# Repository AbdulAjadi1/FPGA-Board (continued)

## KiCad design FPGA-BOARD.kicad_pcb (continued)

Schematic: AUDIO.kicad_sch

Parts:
C1, C2, C187, C189, C190, C191: 100nF; C_0201_0603Metric; LCSC PN c307380
C3: 820pF 5%; C_0402; LCSC PN c307452
C52: GA342DR7GF102KW02L; CAPC4520X220N; LCSC PN C237595
C175, C178: 1nF 5%; C_0402; LCSC PN c76947
C177: 150pF 5%; C_0402; LCSC PN c76951
C179: 100uF; C_0805; LCSC PN c141660
C180: T491B157M006AT; CAPMP3.7X2.8_2.1N_KEM
C182: 1uF 10V; C_0402; LCSC PN C52923
C183, C186: 100nF 10V; C_0402; LCSC PN C77020
C184: 10nF; C_0201_0603Metric; LCSC PN c85930
C185: 4.7uF; C_0402; LCSC PN C2858031
C188: 2.2uF; C_0402; LCSC PN c170151
CR3: BZT52C12-7-F; SOD123_DIO; LCSC PN C19077410
F2: PRG18BB330MB1RB; FUSE_PRG-18_MUR; LCSC PN C133974
J9: SJ1-3525NG; CUI_SJ1-3525NG
J15: USB-A-S-X-X-SM2; SAMTEC_USB-A-S-X-X-SM2; PARTREV T; LCSC PN C6906824
Q10: DMG2305UX-13; DMG2305UX_13; PARTREV 09/2018; LCSC PN C144153
R3, R16, R200, R201: 0; R_0402; LCSC PN C106231
R9: 1.3K 1%; R_0402; LCSC PN C185455
R10, R196: 2K 1%; R_0402; LCSC PN C60488
R11, R193: 10K 1%; R_0402; LCSC PN C60490
R12: 10.7K 1%; R_0402; LCSC PN C270654
R194, R195: 26.1K 1%; R_0402; LCSC PN C155697
R197: 100K; R_0402; LCSC PN C60491
R198: 1MEG; R_0402; LCSC PN C138033
R199: 330K; R_0402; LCSC PN c138006
R202: 4.7K; R_0201_0603Metric; LCSC PN C138135
R203: 1K; R_0402; LCSC PN C106235
U21: NC7WZ07P6X; MPN NC7WZ07P6X; LCSC PN C95342
U25: TPS2051BDBVR; DBV0005A_L; LCSC PN C24593
U26: TUSB1210BRHBT; RHB32_3P45X3P45; LCSC PN C2671015
U30: TPD4E05U06DQAR; IC_TPD4E05U06DQAR; PARTREV N; LCSC PN C138714
U36: AD8592ARM; RM_10_ADI
Y4: ABM8G-26.000MHZ-18-D2Y-T; CRYSTAL_ABM8G_ABR; LCSC PN C1985426

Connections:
+3V3: C184.2, C187.2, U26.20 (VDD33), U26.21 (VBAT), Y4.1, Y4.4 (VDD); also elsewhere on the board
+5V: C186.2, U25.5 (IN); also elsewhere on the board
AUD_PWM: U21.1 (A1); also elsewhere on the board
AUD_SD: U36.5, U36.6; also elsewhere on the board
AVCC3V3: C1.1, C2.1, R9.2, U21.5 (VCC), U36.10 (V+); also elsewhere on the board
GNDREF: C1.2, C2.2, C3.2, C52.1, C177.2, C180.2, C184.1, C185.1, C186.1, C187.1, C188.1, C189.1, C190.1, C191.1, J9.1, J15.04 (GND), R10.2, R193.1, R196.1, R197.2, R198.2, R199.2, R202.1, U21.2 (GND), U25.2 (GND), U26.23 (ID), U26.33 (EPAD), U26.V, U30.3 (GND), U30.8 (GND), U30.10 (NC_10), U36.4 (V-), Y4.2 (GND); also elsewhere on the board
unnamed: C175.1, R11.2, R12.1
unnamed: C175.2, R16.2, R194.2, U36.1
unnamed: C178.1, R194.1, R195.2
unnamed: C179.2, F2.1, R196.2
unnamed: C182.1, C183.1, CR3.2, Q10.1, R199.1, R200.2
unnamed: F2.2, J9.2
unnamed: J9.3, R197.1
unnamed: R3.2, R9.1, R10.1, R11.1
unnamed: R201.1, Y4.3
unnamed: R3.1, U21.6 (Y1)
unnamed: R202.2, U25.4 (EN), U26.17 (CPEN)
unnamed: C188.2, U26.12 (VDD15)
unnamed: C3.1, R12.2, U36.3 (+)
unnamed: R16.1, R193.2, U36.2 (-)
unnamed: C177.1, R195.1, U36.7 (+)
unnamed: C178.2, C179.1, U36.8 (-), U36.9
USBHOST_CLK: U26.26 (CLOCK); also elsewhere on the board
USBHOST_DATA0: U26.3 (DATA0); also elsewhere on the board
USBHOST_DATA1: U26.4 (DATA1); also elsewhere on the board
USBHOST_DATA2: U26.5 (DATA2); also elsewhere on the board
USBHOST_DATA3: U26.6 (DATA3); also elsewhere on the board
USBHOST_DATA4: U26.7 (DATA4); also elsewhere on the board
USBHOST_DATA5: U26.9 (DATA5); also elsewhere on the board
USBHOST_DATA6: U26.10 (DATA6); also elsewhere on the board
USBHOST_DATA7: U26.13 (DATA7); also elsewhere on the board
USBHOST_DIR: U26.31 (DIR); also elsewhere on the board
USBHOST_N: J15.02 (D-), U26.19 (DM), U30.2 (D1-)
USBHOST_NXT: U26.2 (NXT); also elsewhere on the board
USBHOST_OC: U25.3 (OC_N); also elsewhere on the board
USBHOST_P: J15.03 (D+), U26.18 (DP), U30.1 (D1+)
USBHOST_RCLK: R201.2, U26.1 (REFCLK)
USBHOST_RESETN: R203.1, U26.27 (RESETB); also elsewhere on the board
USBHOST_STP: U26.29 (STP); also elsewhere on the board
USBHOST_VBUS: C180.1, C183.2, C185.2, J15.01 (VCC), Q10.3, U26.22 (VBUS), U30.4 (D2+)
USB_SHIELD: C52.2, J15.S1 (SHIELD), J15.S2 (SHIELD__1), R198.1
USB_VCC5V0: C182.2, CR3.1, Q10.2, R200.1, U25.1 (OUT)
VCC1V8_IO: C189.2, C190.2, C191.2, R203.2, U26.11 (CS), U26.14 (CFG), U26.28 (VDD18), U26.30 (VDD18), U26.32 (VDDIO); also elsewhere on the board

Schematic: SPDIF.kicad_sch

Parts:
C10, C11: 100nF 10V; C_0402; LCSC PN C77020
L1: 47uH; IND_TAIYO_CBC2012_TAY; Tolerance ±10%; Part SDFL2012T220KTF; LCSC C32375
R52: 5.6K; R_0402; LCSC PN C163457
U5: TOTX1950AF; TOTX1950AF_TOS
U6: TORX1950AF; TORX1950AF_TOS

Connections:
+3V3: C10.2, C11.2, L1.2, R52.2, U5.3 (VCC); also elsewhere on the board
GNDREF: C10.1, C11.1, U5.1 (GND), U6.2 (GND1), U6.4 (GND2), U6.5 (CASE), U6.6 (CASE); also elsewhere on the board
unnamed: R52.1, U5.2 (RES_LED)
unnamed: L1.1, U6.3 (VCC)
SPDIF_RX: U6.1 (OUTPUT); also elsewhere on the board
SPDIF_TX: U5.4 (INPUT); also elsewhere on the board

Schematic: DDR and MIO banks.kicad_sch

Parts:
BTNR1: PTS645SK50SMTR92LFS; SW_PTS645SK50SMTR92LFS; LCSC PN C221872
C4, C9, C176: 100nF; C_0201_0603Metric; LCSC PN c307380
C5, C8: 10nF; C_0201_0603Metric; LCSC PN c85930
J4: Conn_01x04_Pin; PinHeader_1x04_P2.54mm_Vertical
J5, J8: Conn_01x02_Pin; PinHeader_1x02_P2.54mm_Vertical
R4, R8, R234, R235, R236, R237, R238, R239: 40.2 1%; R_0402; LCSC PN C274892
R5: 100 1%; R_0402; LCSC PN C106232
R6, R7: 80.6 1%; R_0402; LCSC PN C843839
R17, R18, R19, R20, R43, R45: 10K 1%; R_0402; LCSC PN C60490
R36, R37, R38, R40, R42, R48, R49: 20K 1%; R_0402; LCSC PN C93942
R39, R41, R46, R47: 1K; R_0402; LCSC PN C106235
R44: 200; R_0402; LCSC PN C114764
R50: 49.9; R_0402; LCSC PN C87044
U1: XC7Z020-1CLG400I__; CLG400_ZYNQ-7000_AMD; LCSC PN C1519081
U23: NC7WZ07P6X; MPN NC7WZ07P6X; LCSC PN C95342
Y2: SG-8018CE_50.0000M-TJHPA; OSC_SG-8018CE_50.0000M-TJHPA; PARTREV 5/22/24; LCSC PN C390511

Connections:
+1V5: R7.1, R17.1; also elsewhere on the board
+3V3: C9.1, C176.1, J4.4, J5.2, J8.2, R36.1, R45.2, R46.2, U23.5 (VCC), Y2.1 (OE), Y2.4 (VCC); also elsewhere on the board
CK_RST: R45.1, U1.D9 (PS_MIO12_500), U23.4 (Y2)
DDR3_A0: U1.N2 (PS_DDR_A0_502); also elsewhere on the board
DDR3_A1: U1.K2 (PS_DDR_A1_502); also elsewhere on the board
DDR3_A2: U1.M3 (PS_DDR_A2_502); also elsewhere on the board
DDR3_A3: U1.K3 (PS_DDR_A3_502); also elsewhere on the board
DDR3_A4: U1.M4 (PS_DDR_A4_502); also elsewhere on the board
DDR3_A5: U1.L1 (PS_DDR_A5_502); also elsewhere on the board
DDR3_A6: U1.L4 (PS_DDR_A6_502); also elsewhere on the board
DDR3_A7: U1.K4 (PS_DDR_A7_502); also elsewhere on the board
DDR3_A8: U1.K1 (PS_DDR_A8_502); also elsewhere on the board
DDR3_A9: U1.J4 (PS_DDR_A9_502); also elsewhere on the board
DDR3_A10: U1.F5 (PS_DDR_A10_502); also elsewhere on the board
DDR3_A11: U1.G4 (PS_DDR_A11_502); also elsewhere on the board
DDR3_A12: U1.E4 (PS_DDR_A12_502); also elsewhere on the board
DDR3_A13: U1.D4 (PS_DDR_A13_502); also elsewhere on the board
DDR3_A14: U1.F4 (PS_DDR_A14_502); also elsewhere on the board
DDR3_BA0: U1.L5 (PS_DDR_BA0_502); also elsewhere on the board
DDR3_BA1: U1.R4 (PS_DDR_BA1_502); also elsewhere on the board
DDR3_BA2: U1.J5 (PS_DDR_BA2_502); also elsewhere on the board
DDR3_CAS: U1.P5 (PS_DDR_CAS_B_502); also elsewhere on the board
DDR3_CKE0: U1.N3 (PS_DDR_CKE_502); also elsewhere on the board
DDR3_CK_N: R5.2, U1.M2 (PS_DDR_CKN_502); also elsewhere on the board
DDR3_CK_P: R5.1, U1.L2 (PS_DDR_CKP_502); also elsewhere on the board
DDR3_CS: U1.N1 (PS_DDR_CS_B_502); also elsewhere on the board
DDR3_D0: U1.E2 (PS_DDR_DQ8_502); also elsewhere on the board
DDR3_D1: U1.G3 (PS_DDR_DQ10_502); also elsewhere on the board
DDR3_D2: U1.E3 (PS_DDR_DQ9_502); also elsewhere on the board
DDR3_D3: U1.H1 (PS_DDR_DQ14_502); also elsewhere on the board
DDR3_D4: U1.H3 (PS_DDR_DQ11_502); also elsewhere on the board
DDR3_D5: U1.J1 (PS_DDR_DQ15_502); also elsewhere on the board
DDR3_D6: U1.H2 (PS_DDR_DQ13_502); also elsewhere on the board
DDR3_D7: U1.J3 (PS_DDR_DQ12_502); also elsewhere on the board
DDR3_D8: U1.E1 (PS_DDR_DQ7_502); also elsewhere on the board
DDR3_D9: U1.C3 (PS_DDR_DQ0_502); also elsewhere on the board
DDR3_D10: U1.D3 (PS_DDR_DQ4_502); also elsewhere on the board
DDR3_D11: U1.A2 (PS_DDR_DQ2_502); also elsewhere on the board
DDR3_D12: U1.C1 (PS_DDR_DQ6_502); also elsewhere on the board
DDR3_D13: U1.A4 (PS_DDR_DQ3_502); also elsewhere on the board
DDR3_D14: U1.D1 (PS_DDR_DQ5_502); also elsewhere on the board
DDR3_D15: U1.B3 (PS_DDR_DQ1_502); also elsewhere on the board
DDR3_DM0: U1.F1 (PS_DDR_DM1_502); also elsewhere on the board
DDR3_DM1: U1.A1 (PS_DDR_DM0_502); also elsewhere on the board
DDR3_DQS0_N: U1.F2 (PS_DDR_DQS_N1_502); also elsewhere on the board
DDR3_DQS0_P: U1.G2 (PS_DDR_DQS_P1_502); also elsewhere on the board
DDR3_DQS1_N: U1.B2 (PS_DDR_DQS_N0_502); also elsewhere on the board
DDR3_DQS1_P: U1.C2 (PS_DDR_DQS_P0_502); also elsewhere on the board
DDR3_ODT0: U1.N5 (PS_DDR_ODT_502); also elsewhere on the board
DDR3_RAS: U1.P4 (PS_DDR_RAS_B_502); also elsewhere on the board
DDR3_RESET: U1.B4 (PS_DDR_DRST_B_502); also elsewhere on the board
DDR3_VREF: C4.1, C5.1, R17.2, R20.1, U1.H6 (PS_DDR_VREF0_502), U1.P6 (PS_DDR_VREF1_502); also elsewhere on the board
DDR3_WE: U1.M5 (PS_DDR_WE_B_502); also elsewhere on the board
ETH_INT_B: U1.E9 (PS_MIO10_500); also elsewhere on the board
ETH_MDC: U1.C10 (PS_MIO52_501); also elsewhere on the board
ETH_MDIO: U1.C11 (PS_MIO53_501); also elsewhere on the board
ETH_RST_B: U1.B5 (PS_MIO9_500); also elsewhere on the board
ETH_RXCK: U1.B17 (PS_MIO22_501); also elsewhere on the board
ETH_RXCTL: U1.D13 (PS_MIO27_501); also elsewhere on the board
ETH_RXD0: U1.D11 (PS_MIO23_501); also elsewhere on the board
ETH_RXD1: U1.A16 (PS_MIO24_501); also elsewhere on the board
ETH_RXD2: U1.F15 (PS_MIO25_501); also elsewhere on the board
ETH_RXD3: U1.A15 (PS_MIO26_501); also elsewhere on the board
ETH_TXCLK: R239.2; also elsewhere on the board
ETH_TXCTL: R235.2; also elsewhere on the board
ETH_TXD0: R234.2; also elsewhere on the board
ETH_TXD1: R236.2; also elsewhere on the board
ETH_TXD2: R237.2; also elsewhere on the board
ETH_TXD3: R238.2; also elsewhere on the board
GNDREF: BTNR1.3, C4.2, C5.2, C8.2, C9.2, C176.2, J4.2, R6.1, R19.2, R20.2, R37.1, R38.1, R39.1, R41.1, R47.1, U23.2 (GND), Y2.2 (GND); also elsewhere on the board
unnamed: BTNR1.1, R44.1
unnamed: J4.1, R46.1, R48.2
unnamed: J4.3, R47.2, R49.2
unnamed: J5.1, R39.2, R40.1
unnamed: J8.1, R41.2, R42.1
unnamed: R7.2, U1.G5 (PS_DDR_VRN_502)
unnamed: R6.2, U1.H5 (PS_DDR_VRP_502)
unnamed: R239.1, U1.A19 (PS_MIO16_501)
unnamed: R234.1, U1.E14 (PS_MIO17_501)
unnamed: R236.1, U1.B18 (PS_MIO18_501)
unnamed: R237.1, U1.D10 (PS_MIO19_501)
unnamed: R238.1, U1.A17 (PS_MIO20_501)
unnamed: R235.1, U1.F14 (PS_MIO21_501)
unnamed: R8.1, U1.D14 (PS_MIO40_501)
unnamed: R4.1, U1.A5 (PS_MIO6_500)
unnamed: R50.2, Y2.3 (OUT)
PS_CLK: R50.1, U1.E7 (PS_CLK_500)
PS_POR_B: U1.C7 (PS_POR_B_500); also elsewhere on the board
PS_RST: R43.2, R44.2, U1.B10 (PS_SRST_B_501), U23.3 (A2)
SD_CCLK: R8.2; also elsewhere on the board
SD_CD: U1.B14 (PS_MIO47_501); also elsewhere on the board
SD_CMD: U1.C17 (PS_MIO41_501); also elsewhere on the board
SD_D0: U1.E12 (PS_MIO42_501); also elsewhere on the board
SD_D1: U1.A9 (PS_MIO43_501); also elsewhere on the board
SD_D2: U1.F13 (PS_MIO44_501); also elsewhere on the board
SD_D3: U1.B15 (PS_MIO45_501); also elsewhere on the board
SPI_CS: U1.A7 (PS_MIO1_500); also elsewhere on the board
SPI_DQ0/MODE3: R40.2, U1.B8 (PS_MIO2_500); also elsewhere on the board
SPI_DQ1/MODE1: R38.2, U1.D6 (PS_MIO3_500); also elsewhere on the board
SPI_DQ2/MODE2: R49.1, U1.B7 (PS_MIO4_500); also elsewhere on the board
SPI_DQ3/MODE0: R48.1, U1.A6 (PS_MIO5_500); also elsewhere on the board
SPI_SCK/MODE4: R4.2, R42.2; also elsewhere on the board
SPI_SCLK_FB/VCFG1: R36.2, U1.D5 (PS_MIO8_500)
UART_RXD_OUT: U1.C8 (PS_MIO15_500); also elsewhere on the board
UART_TXD_IN: U1.C5 (PS_MIO14_500); also elsewhere on the board
USBHOST_CLK: U1.A11 (PS_MIO36_501); also elsewhere on the board
USBHOST_DATA0: U1.A14 (PS_MIO32_501); also elsewhere on the board
USBHOST_DATA1: U1.D15 (PS_MIO33_501); also elsewhere on the board
USBHOST_DATA2: U1.A12 (PS_MIO34_501); also elsewhere on the board
USBHOST_DATA3: U1.F12 (PS_MIO35_501); also elsewhere on the board
USBHOST_DATA4: U1.C16 (PS_MIO28_501); also elsewhere on the board
USBHOST_DATA5: U1.A10 (PS_MIO37_501); also elsewhere on the board
USBHOST_DATA6: U1.E13 (PS_MIO38_501); also elsewhere on the board
USBHOST_DATA7: U1.C18 (PS_MIO39_501); also elsewhere on the board
USBHOST_DIR: U1.C13 (PS_MIO29_501); also elsewhere on the board
USBHOST_NXT: U1.E16 (PS_MIO31_501); also elsewhere on the board
USBHOST_OC: U1.C6 (PS_MIO11_500); also elsewhere on the board
USBHOST_RESETN: U1.D16 (PS_MIO46_501); also elsewhere on the board
USBHOST_STP: U1.C15 (PS_MIO30_501); also elsewhere on the board
VCC1V8_IO: R18.1, R43.1; also elsewhere on the board
VCFG0: R37.2, U1.D8 (PS_MIO7_500)
VREF0V9: C8.1, R18.2, R19.1, U1.E11 (PS_MIO_VREF_501)

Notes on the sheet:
VCC1V5
VCC1V8_IO
VCC3V3

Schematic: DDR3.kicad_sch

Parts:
C34, C35: 10nF; C_0201_0603Metric; LCSC PN c85930
C36, C37, C38, C39, C40, C41, C42, C43, C44, C45, C46, C47, C48, C49, C50, C51: 47nF; C_0201_0603Metric; LCSC PN C88917
C82, C83: 470nF; C_0201_0603Metric; LCSC PN C5383023
C84: 4.7uF; C_0402; LCSC PN C2858031
IC1: IS43TR16256B-125KBLI; BGA96C80P9X16_900X1300X120; Mouser_Part_Number 870-43T16256B125KBLI
R95: 240 1%; R_0402; LCSC PN C114755
R96: 4.7K; R_0201_0603Metric; LCSC PN C138135

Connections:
+1V5: C34.1, C36.1, C37.1, C38.1, C39.1, C40.1, C41.1, C42.1, C43.1, C44.1, C45.1, C46.1, C47.1, C48.1, C49.1, C50.1, C51.1, C82.1, C83.1, C84.1, IC1.A1 (VDDQ_1), IC1.A8 (VDDQ_2), IC1.B2 (VDD_1), IC1.C1 (VDDQ_3), IC1.C9 (VDDQ_4), IC1.D2 (VDDQ_5), IC1.D9 (VDD_2), IC1.E9 (VDDQ_6), IC1.F1 (VDDQ_7), IC1.G7 (VDD_3), IC1.H2 (VDDQ_8), IC1.H9 (VDDQ_9), IC1.K2 (VDD_4), IC1.K8 (VDD_5), IC1.N1 (VDD_6), IC1.N9 (VDD_7), IC1.R1 (VDD_8), IC1.R9 (VDD_9); also elsewhere on the board
DDR3_A0: IC1.N3 (A0); also elsewhere on the board
DDR3_A1: IC1.P7 (A1); also elsewhere on the board
DDR3_A2: IC1.P3 (A2); also elsewhere on the board
DDR3_A3: IC1.N2 (A3); also elsewhere on the board
DDR3_A4: IC1.P8 (A4); also elsewhere on the board
DDR3_A5: IC1.P2 (A5); also elsewhere on the board
DDR3_A6: IC1.R8 (A6); also elsewhere on the board
DDR3_A7: IC1.R2 (A7); also elsewhere on the board
DDR3_A8: IC1.T8 (A8); also elsewhere on the board
DDR3_A9: IC1.R3 (A9); also elsewhere on the board
DDR3_A10: IC1.L7 (A10/AP); also elsewhere on the board
DDR3_A11: IC1.R7 (A11); also elsewhere on the board
DDR3_A12: IC1.N7 (A12/BC#); also elsewhere on the board
DDR3_A13: IC1.T3 (A13); also elsewhere on the board
DDR3_A14: IC1.T7 (A14); also elsewhere on the board
DDR3_BA0: IC1.M2 (BA0); also elsewhere on the board
DDR3_BA1: IC1.N8 (BA1); also elsewhere on the board
DDR3_BA2: IC1.M3 (BA2); also elsewhere on the board
DDR3_CAS: IC1.K3 (CAS#); also elsewhere on the board
DDR3_CKE0: IC1.K9 (CKE); also elsewhere on the board
DDR3_CK_N: IC1.K7 (CK#); also elsewhere on the board
DDR3_CK_P: IC1.J7 (CK); also elsewhere on the board
DDR3_CS: IC1.L2 (CS#); also elsewhere on the board
DDR3_D0: IC1.E3 (DQL0); also elsewhere on the board
DDR3_D1: IC1.F7 (DQL1); also elsewhere on the board
DDR3_D2: IC1.F2 (DQL2); also elsewhere on the board
DDR3_D3: IC1.F8 (DQL3); also elsewhere on the board
DDR3_D4: IC1.H3 (DQL4); also elsewhere on the board
DDR3_D5: IC1.H8 (DQL5); also elsewhere on the board
DDR3_D6: IC1.G2 (DQL6); also elsewhere on the board
DDR3_D7: IC1.H7 (DQL7); also elsewhere on the board
DDR3_D8: IC1.D7 (DQU0); also elsewhere on the board
DDR3_D9: IC1.C3 (DQU1); also elsewhere on the board
DDR3_D10: IC1.C8 (DQU2); also elsewhere on the board
DDR3_D11: IC1.C2 (DQU3); also elsewhere on the board
DDR3_D12: IC1.A7 (DQU4); also elsewhere on the board
DDR3_D13: IC1.A2 (DQU5); also elsewhere on the board
DDR3_D14: IC1.B8 (DQU6); also elsewhere on the board
DDR3_D15: IC1.A3 (DQU7); also elsewhere on the board
DDR3_DM0: IC1.E7 (DML); also elsewhere on the board
DDR3_DM1: IC1.D3 (DMU); also elsewhere on the board
DDR3_DQS0_N: IC1.G3 (DQSL#); also elsewhere on the board
DDR3_DQS0_P: IC1.F3 (DQSL); also elsewhere on the board
DDR3_DQS1_N: IC1.B7 (DQSU#); also elsewhere on the board
DDR3_DQS1_P: IC1.C7 (DQSU); also elsewhere on the board
DDR3_ODT0: IC1.K1 (ODT); also elsewhere on the board
DDR3_RAS: IC1.J3 (RAS#); also elsewhere on the board
DDR3_RESET: IC1.T2 (RESET#), R96.1; also elsewhere on the board
DDR3_VREF: C34.2, C35.1, IC1.H1 (VREFDQ), IC1.M8 (VREFCA); also elsewhere on the board
DDR3_WE: IC1.L3 (WE#); also elsewhere on the board
GNDREF: C35.2, C36.2, C37.2, C38.2, C39.2, C40.2, C41.2, C42.2, C43.2, C44.2, C45.2, C46.2, C47.2, C48.2, C49.2, C50.2, C51.2, C82.2, C83.2, C84.2, IC1.A9 (VSS_1), IC1.B1 (VSSQ_1), IC1.B3 (VSS_2), IC1.B9 (VSSQ_2), IC1.D1 (VSSQ_3), IC1.D8 (VSSQ_4), IC1.E1 (VSS_3), IC1.E2 (VSSQ_5), IC1.E8 (VSSQ_6), IC1.F9 (VSSQ_7), IC1.G1 (VSSQ_8), IC1.G8 (VSS_4), IC1.G9 (VSSQ_9), IC1.J2 (VSS_5), IC1.J8 (VSS_6), IC1.M1 (VSS_7), IC1.M9 (VSS_8), IC1.P1 (VSS_9), IC1.P9 (VSS_10), IC1.T1 (VSS_11), IC1.T9 (VSS_12), R95.2, R96.2; also elsewhere on the board
unnamed: IC1.L8 (ZQ), R95.1

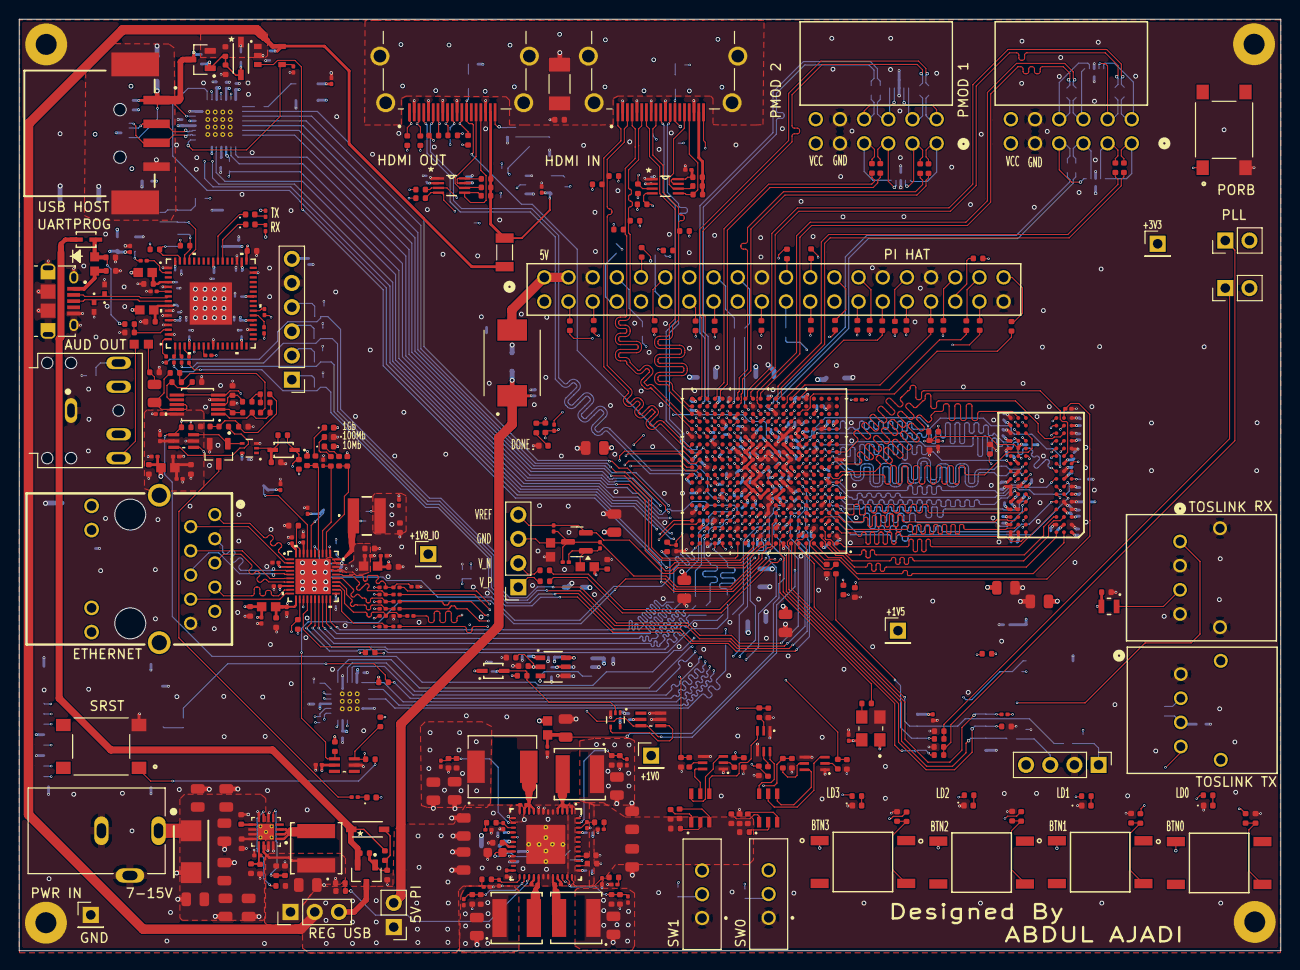
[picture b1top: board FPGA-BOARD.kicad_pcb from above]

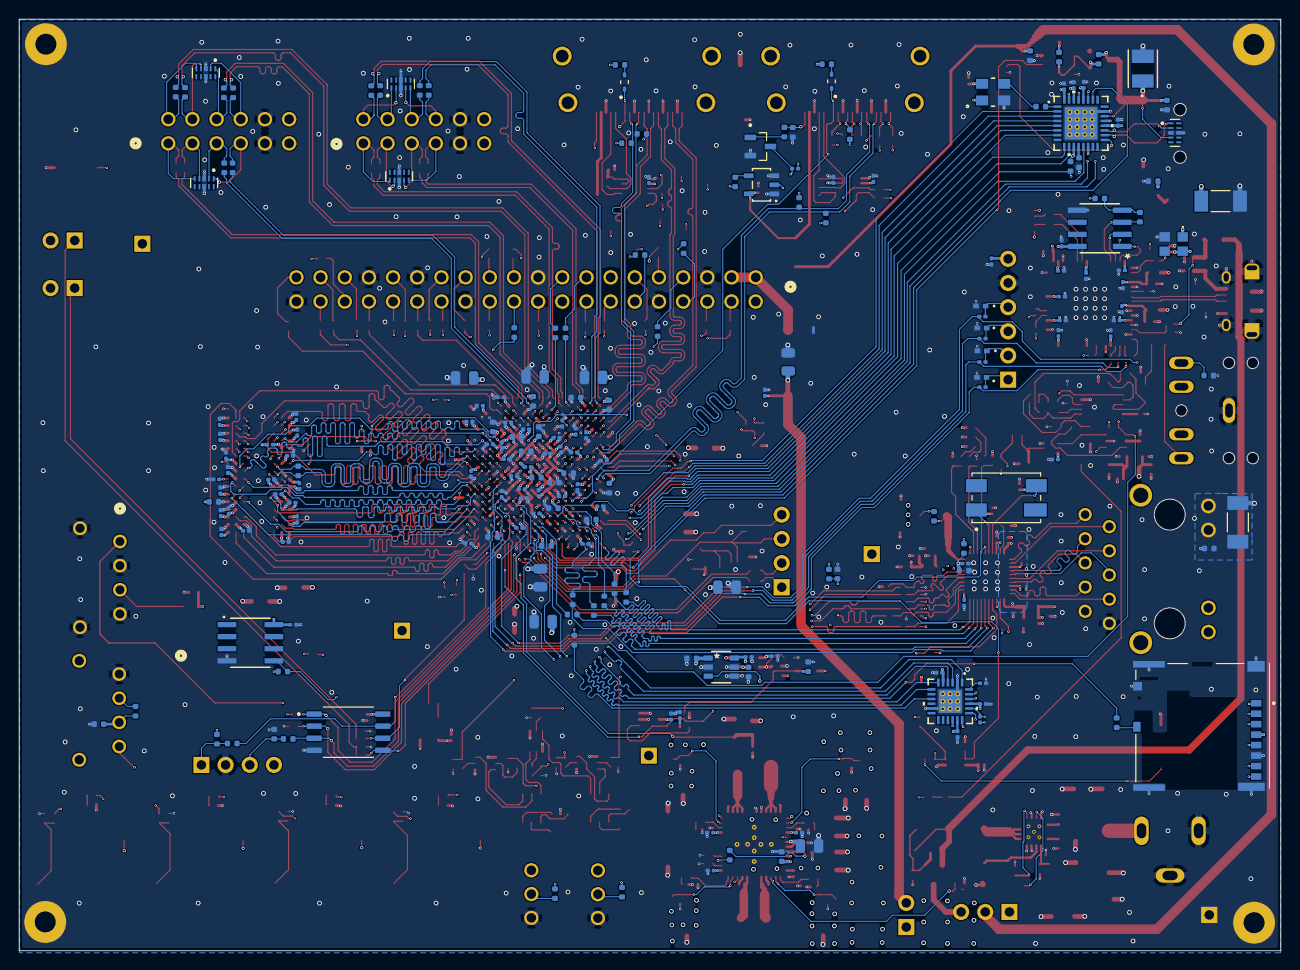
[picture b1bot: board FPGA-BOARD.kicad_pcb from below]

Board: 8 copper layers, 132.6 x 97.9 mm, 593 parts (207 on the bottom side), 463 nets.

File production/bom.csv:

Designator,Footprint,Quantity,Value,LCSC Part #
"C1, C12, C13, C14, C15, C155, C162, C165, C168, C17, C171, C174, C176, C18, C187, C189, C190, C191, C2, C201, C202, C204, C205, C206, C208, C209, C213, C215, C216, C217, C218, C22, C220, C221, C222, C223, C224, C225, C226, C227, C228, C229, C23, C230, C231, C232, C233, C24, C25, C28, C32, C33, C4, C53, C54, C55, C56, C57, C63, C65, C68, C70, C71, C73, C75, C76, C78, C79, C80",C_0402,69,100nF,
"C10, C11",C_0402,2,.1uF,
"C100, C101, C102, C103, C104, C105, C106, C107, C108, C109, C110, C111, C112, C113, C26, C82, C83, C87, C88, C89, C90, C91, C92, C93, C94, C95, C96, C97, C98, C99",C_0402,30,470nF,
"C114, C115, C117, C118, C119, C120, C121, C122, C123, C124, C126, C127, C172, C207, C210, C211, C212, C214, C219, C58, C64, C67, C69, C72, C74, C77, C81, C86",C_0402,28,4.7uF,
"C116, C84",C_0402,2,4.7nF,
"C125, C138",C_0402,2,47uF,
"C128, C129, C130, C131, C132, C133, C134, C135, C136, C179, C85",C_0402,11,100uF,
"C137, C192, C193, C194, C195, C196, C197, C198, C199",C_0402,9,10uF,
"C139, C140, C141, C142, C156, C164, C167, C170, C200",C_0402,9,22uF,
"C143, C31",C_0402,2,10uF/10V,
C144,C_0402,1,1uF/10V,
C145,C_0402,1,3.3uF/10V,
"C146, C27",C_0402,2,4.7uF/10V,
C147,C_0402,1,1.5nF,
"C148, C154, C157, C160",C_0402,4,33nF,
"C149, C151, C153, C159, C161, C163, C166, C169",C_0402,8,10pF,
C150,C_0402,1,150pF,
C152,C_0402,1,1.2nF,
C158,C_0402,1,330pF,
"C16, C181, C66",C_0402,3,1nF,
"C173, C19, C20, C21",C_0402,4,1uF,
"C175, C178",C_0402,2,1nF 5%,
C177,C_0402,1,150pF 5%,
C180,CAPMP3.7X2.8_2.1N_KEM,1,T491B157M006AT,digi
C182,C_0402,1,1uF 10V,
"C183, C186",C_0402,2,100nF 10V,
"C184, C34, C35, C5, C8, C9",C_0402,6,10nF,
C185,C_0402,1,4.7uF 10V,
C188,C_0402,1,2.2uF,
C203,C_0402,1,1nF/2kV,
C29,C_0402,1,22nF,
C3,C_0402,1,820pF 5%,
C30,C_0402,1,0.1uF,
"C36, C37, C38, C39, C40, C41, C42, C43, C44, C45, C46, C47, C48, C49, C50, C51",C_0402,16,47nF,
C52,C_0402,1,1nF 250V,
"C59, C60, C61, C62",C_0402,4,27pF,
C6,C_0402,1,1uF /10V,
C7,C_0402,1,1uF / 10V,
"CR1, CR2",USC_TOS,2,1SS352,C15885
"CR3, CR4",ZDO_SOD123_DIO,2,DDZ9699-7,C460860
CR5,CRYSTAL_TXC_7M,1,7M-26.000MAAJ-T,digi
"CR6, CR7",CR_050R3C2P_AVX,2,GG0402050R3C2P,
"D1, D25, D28, D32, D33, D4, D5, D6, PWR1, RX1, TX1",0402,11,LED,
"D26, D27",SODFL1608X70N,2,BAS16XV2T1G,C152479
D37,DIOM5436X244N,1,SMBJ15CA-E3_52,C435933
"D7, D8",LED_SMLV56_ROM,2,SMLVN6RGB,digi
DONE1,0402,1,Green,
F1,PTS120630V012,1,PTS120630V012,digi
F2,FUSE_PRG-18_MUR,1,PRG18BB330MB1RB,C133974
"FL1, FL2, FL3, FL4, FL5, FL6, FL7, FL8",BEADC1608X95N,8,600Ohm/100MHz,digi
IC1,BGA96C80P9X16_900X1300X120,1,IS43TR16256B-125KBLI,C17490362
J1,CUI_PJ-102AH,1,PJ-102AH,digi
"J10, J11",AMPHENOL_10029449-001RLF,2,10029449-001RLF,C428493
J12,HALO_FASTJACK,1,HFJ11-1G01ERL,digi
J13,MOLEX_503398-1892,1,503398-1892,C428492
J14,CONN_PRT-14017_SPK,1,PRT-14017,digi
J15,SAMTEC_USB-A-S-X-X-SM2,1,USB-A-S-X-X-SM2,digi
J16,AMPHENOL_10118194-0001LF,1,10118194-0001LF,
"J17, J5, J8",PinHeader_1x02_P2.54mm_Vertical,3,Conn_01x02_Pin,
J2,PinHeader_1x01_P2.54mm_Vertical,1,Conn_01x01_Pin,
J3,PinHeader_1x03_P2.54mm_Vertical,1,Conn_01x03_Pin,
J4,PinHeader_1x04_P2.54mm_Vertical,1,Conn_01x04_Pin,
J6,PinSocket_1x04_P2.54mm_Vertical,1,ADC_CONN,
J7,PinSocket_1x08_P2.54mm_Vertical,1,POWER_CONN,
J9,CUI_SJ1-3525NG,1,SJ1-3525NG,digi
L1,L_0402,1,47uH,C32375
L10,IND_TYS60282_LRD,1,TYS60282R2N-10/2.2uH,digi
L2,SRN4018,1,SRN4018-3R3M,digi
L3,IND_TAIYO_NR5040_TAY,1,NR5040T4R7N / 4.7uH,digi
L5,IND_SRP4020_BRN,1,SRP4020TA-1R5M,
"L6, L7",IND_TAIYO_NR5040_TAY,2,NR5040T4R7N/ 4.7uH,C223063
"P1, P2",CONN_PPPC062LJBN-RC_SUL,2,PMOD-Device-x2-Type-Generic-Alt,digi
"Q10, Q7",DMG2305UX_13,2,DMG2305UX-13,C144153
"Q8, Q9",FDV301N,2,FDV301N,C15310
"R1, R13, R14, R2",R_0402,4,330,
R10,R_0402,1,2K 1%,
R100,R_0402,1,180K,
R101,R_0402,1,75K,
R102,R_0402,1,150K,
R103,R_0402,1,8.87K/1%,
"R104, R108",R_0402,2,10.2K/1%,
R105,R_0402,1,20K/1%,
R106,R_0402,1,16K/1%,
R107,R_0402,1,31.6K/1%,
R109,R_0402,1,8.2K/1%,
"R11, R17, R18, R19, R20",R_0402,5,10K 1%,
R110,R_0402,1,30K/1%,
"R111, R219, R220",R_0402,3,470,
R112,R_0402,1,1M,
"R113, R124, R131, R15, R154, R193, R206, R207, R208, R209, R21, R210, R211, R216, R22, R23, R24, R25, R26, R27, R28, R29, R43, R45, R86, R99",R_0402,26,10k,
"R114, R115",R_0402,2,220,
"R116, R155, R160, R167, R168, R169, R178, R179, R186, R202, R53, R54, R84, R93, R96",R_0402,15,4.7K,
"R117, R125, R126, R132, R133, R170",R_0402,6,1.5K,
"R118, R119, R120, R121",R_0402,4,100,
R12,R_0402,1,10.7K 1%,
"R122, R123",R_0402,2,140,
"R127, R128, R129, R130, R152, R203, R218, R39, R41, R46, R47",R_0402,11,1K,
"R134, R135, R136, R137, R138, R139, R140, R141, R144, R145, R146, R147, R148, R149, R150, R151, R50",R_0402,17,49.9,
"R142, R143",R_0402,2,27K,
"R153, R181, R198",R_0402,3,1MEG,
"R156, R16, R161, R162, R163, R164, R165, R166, R171, R180, R200, R201, R204, R205, R3, R67, R68, R69, R70, R71, R72, R73, R74, R75, R76, R77, R78, R79, R80, R81, R82, R91",R_0402,32,0,
"R157, R158, R159",R_0402,3,1.2K,
R172,R_0402,1,2.49K 1%,
"R173, R174, R175, R176, R177",R_0402,5,390,
"R182, R183, R189, R190, R191, R192, R33, R34, R35, R55, R56, R57, R61, R62, R63, R64, R65, R66",R_0402,18,2.2K,
"R184, R44",R_0402,2,200,
R185,R_0402,1,47K,
"R187, R92",R_0402,2,15K,
R188,R_0402,1,82,
"R194, R195",R_0402,2,26.1K 1%,
R196,R_0402,1,2K,
"R197, R212, R213, R214, R215, R221, R222, R223, R224, R225, R226, R227, R228, R229, R230, R231, R232, R233, R83, R98",R_0402,20,100K,
R199,R_0402,1,330K,
R217,R_0402,1,2k2,
"R234, R235, R236, R237, R238, R239, R4",R_0402,7,40.2,
"R240, R241",R_0402,2,200k,
"R30, R58",R_0402,2,86.6,
"R31, R59",R_0402,2,150,
"R32, R60",R_0402,2,75,
"R36, R37, R38, R40, R42, R48, R49, R85",R_0402,8,20K,
"R5, R6, R7",R_0402,3,80.6 1%,
R51,R_0402,1,12K 1%,
R52,R_0402,1,5.6K,
R8,R_0402,1,40.2 1%,
R87,R_0402,1,13.3K/1%,
R88,R_0402,1,69.8K/1%,
R89,R_0402,1,10k/1%,
R9,R_0402,1,1.3K 1%,
R90,R_0402,1,62k/1%,
R94,R_0402,1,680,
R95,R_0402,1,240 1%,
R97,R_0402,1,33K,
"S1, S2, S6, S7, S8, S9",SW_PTS645SK50SMTR92LFS,6,PTS645SK50SMTR92LFS,digi
"SW0, SW1",SW_EG1218,2,SW_SPDT,digi
U1,CLG400_ZYNQ-7000_AMD,1,XC7Z020-1CLG400I__,C1519081
U10,RM_10_ADI,1,AD8647ARMZ-REEL,digi
U11,SC-74A_318BQ_ONS,1,NC7SZ125M5X,C7420
U12,RTL8211F-CG_RTK,1,RTL8211F-CG,C187932
U13,RTW24_2P45X2P45,1,TXS02612RTWR,C140276
U14,TLV62130RGTT,1,TLV62130RGTT,C122479
U15,SOT-23-5,1,LP5907MFX-3.3,C80670
U16,SOT-23,1,REF3012,C34674
"U17, U21, U23",NC7WZ07P6X,3,NC7WZ07P6X,C19829570
"U18, U19",SOT553-5_ONS,2,NL17SZ17XV5T2G,digi
U2,VDFN6_3P2X2P5_MCH,1,DSC1122CI5-050.0000T,
U20,MLP6_2X2_ONS,1,FPF1018,digi
U22,RGZ0048B,1,TPS65400RGZT,C201658
"U24, U8",SOP50P310X90-8N,2,TXS0102DCUR,digi
U25,DBV0005A_L,1,TPS2051BDBVR,C24593
U26,RHB32_3P45X3P45,1,TUSB1210BRHBT,C2671015
"U27, U28, U29, U30, U35",IC_TPD4E05U06DQAR,5,TPD4E05U06DQAR,C138714
U3,64QFN_FT2232HQ_FTD,1,FT2232HQ,
"U31, U32, U33",SOT236,3,MBT3904DW1T1G,C110150
U36,SOT-23-5_MC_MCH,1,MIC5504-3.3YM5-TR,
U37,SOT-23-6_MC_MCH,1,93LC56BT-I/OT,
U38,KC2016K_KYO,1,KC2016K12.0000C1GE00,
"U39, U42, U43, U44, U45",DBV0006A_L,5,SN74LVC1T45DBVR,
U4,SOIC8_4P9X3P9MC_MCH,1,ATSHA204A-SSHCZ-T,C616025
U40,NC7WZ07P6X,1,NC7WZ07P6X,NC7WZ07P6X
U41,SC-74A_318BQ_ONS,1,NC7SZ125M5X,
"U46, U47",US8-8_2P1X2P4_ONS,2,NC7WZ126K8X,
U5,TOTX1950AF_TOS,1,TOTX1950AF,mouser
U6,TORX1950AF_TOS,1,TORX1950AF,mouser
U7,SO3016_INF,1,S25FL128SAGMFI000,C393875
U9,SIP32510DT-T1-GE3_VIS,1,SIP32510DT-T1-GE3,digi
Y1,XTAL_ABMM-25.000MHZ-B2-T,1,ABMM-25.000MHZ-B2-T,C596927

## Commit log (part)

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2025-02-17 initial commit of fpga-board
2025-02-17 ki-cad files
2025-02-17 reset repository
2025-02-17 kicad schmatic files
2025-02-17 ki-cad schematic ver 3
2025-02-24 added git version control steps
2025-02-27 added Arty pmod, useri/o
2025-02-27 updated file name for PMOD, USER I/O
2025-03-05 power regulation schematic added
2025-03-16 DDR3 Schematic sheet added
2025-03-17 Added FPGA-POWER Schematic
2025-03-18 Power Regulation sheet 2 added
2025-03-18 removed old reference design
2025-03-18 version 2 deleted
2025-03-18 added xc7z020-1clg400i symbol and footprint
2025-03-23 assigned footprints for power section and ddr3
2025-03-23 footprints added to project specific library
2025-03-25 added symbol and footprint folders for common components in schematics
2025-03-31 added fpga banks and final fpga symbol
2025-03-31 hdmi added
2025-04-07 spdif fpga bansks
2025-04-10 All pages complete , pi header left
2025-04-11 schematic pages for review
2025-04-11 Schematic update for review
2025-04-11 added schmatic pdf arty z7
2025-04-13 added audio out and usb
2025-09-09 updated schematic and layout
2025-09-09 removed drc errors
2025-09-10 restructuring
2025-10-31 Updated PCB layout and schematic
2025-11-05 new layout by abdul
2025-11-07 Initial Files
2025-11-10 hdmi,pmod raspberrypi gpio, led fanout first draft done
2025-11-17 weekend update
2025-11-18 update before kicad ver9 download
2025-11-25 Layout update
2025-11-25 update on ftdi usb-jtag programming section
2025-12-17 ready for manufacturing
2026-01-01 ignore
2026-01-01 gitignore
2026-01-01 remove
2026-01-01 Add 3D board render
2026-01-01 3d render
